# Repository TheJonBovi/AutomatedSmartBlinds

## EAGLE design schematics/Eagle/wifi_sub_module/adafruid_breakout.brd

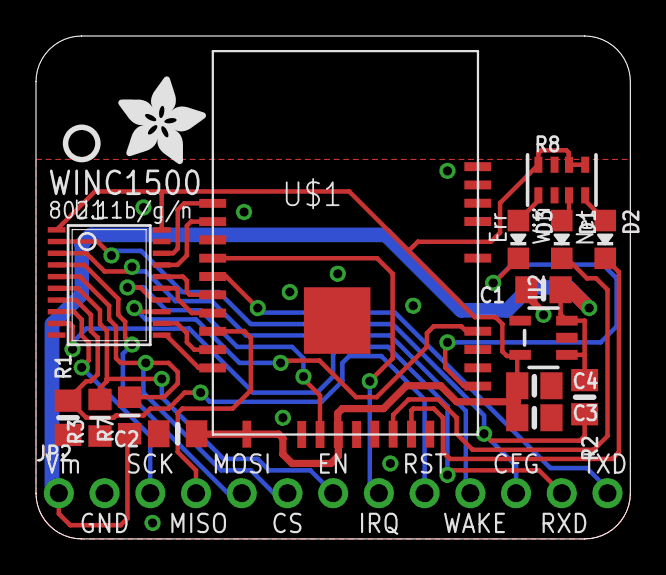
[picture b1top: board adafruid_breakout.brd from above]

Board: 2 copper layers, 33.0 x 27.9 mm, 19 parts (1 on the bottom side), 28 nets.

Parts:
C1, C3: 10uF; 0805-NO
C2: 10uF; 0805_10MGAP
C4: 0.1uF; 0805-NO
D1: green; CHIPLED_0805_NOOUTLINE
D2: Yellow; CHIPLED_0805_NOOUTLINE
D3: Red; CHIPLED_0805_NOOUTLINE
JP2: 1X13_ROUND_70
R1, R2: 100K; 0805-NO
R3, R7: 100K; _0805MP
R8: 1K; RESPACK_4X0603
U1: 74LVC245; TSSOP20
U2: AP2112-3.3; SOT23-5
U$1: ATWINC1500_MR210PB; ATWINC1500_MR210PA
U$4: ADAFRUIT_5MM
U$5: PCBFEAT-REV-040
U$6: ADAFRUIT_TEXT_20MM

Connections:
!IRQ: JP2.8, U$1.J13
+3V3: C2.1, C3.1, C4.1, R8.5, R8.6, R8.8, U1.1, U1.20, U2.5, U$1.J20, U$1.J23
+5V: C1.1, JP2.1, R2.1, R7.1, U2.1, U2.3
CFG_3V: U1.18, U$1.J10
CFG_5V: JP2.11, R2.2, U1.2
CS_3V: U1.15, U$1.J16
CS_5V: JP2.6, R7.2, U1.5
EN_3V: U1.14, U$1.J22
EN_5V: JP2.7, R3.2, U1.6
GND: C1.2, C2.2, C3.2, C4.2, JP2.2, R1.1, R3.1, U1.10, U1.19, U2.2, U$1.J9, U$1.J12, U$1.J28, U$1.MTGND
GPIO15: D1.C, U$1.J26
GPIO16: D2.C, U$1.J27
GPIO18: D3.C, U$1.J1
MISO: JP2.4, U$1.J17
MOSI_3V: U1.16, U$1.J15
MOSI_5V: JP2.5, U1.4
unnamed: D3.A, R8.1
unnamed: D2.A, R8.4
unnamed: D1.A, R8.3
RST_3V: U1.13, U$1.J4
RST_5V: JP2.9, R1.2, U1.7
RXD_3V: U1.11, U$1.J19
RXD_5V: JP2.12, U1.9
SCK_3V: U1.12, U$1.J18
SCK_5V: JP2.3, U1.8
TXD: JP2.13, U$1.J14
WAKE_3V: U1.17, U$1.J11
WAKE_5V: JP2.10, U1.3

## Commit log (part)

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2019-10-24 added documentation folder
    added folder and PIC32MZ datasheet as an example.
2019-10-25 Added datasheets
    Added datasheets for Drew components.
    Started MPLAB project for EFG version of software.
2019-10-31 Create 50002616A(WINC1500 Xplained Pro).pdf
    Added datashhet, this is a description of module and links to all other Datasheets
2019-10-31 Create Atmel-42420-WINC1500-Software-Design-Guide_UserGuide(WINC1500).pdf
    Software specs and design considerations
2019-10-31 Create PIC32MZ to WINC1500(WINC1500 to PIC).pdf
    examples of connecting to PIC MZ
2019-10-31 Create Wi-Fi_Network_Controller_Software_Prog_Guide(WINC1500).pdf
    Software programming guide
2019-10-31 Create junior_project.xlsx
    Gantt Chart started week 5 for schedule will update every meeting
2019-11-04 created main, config and ISR files
    Created the basis for the rest of the project, including a main routine to perform the RTS loop, as well as a config and ISR file to handle their respective duties.
    Also configured PBCLK3 and T2 and T3 according to CST337 lab as a proof-of-concept test. All configurations appear to be working so far in the simulator.
    Also added a specific datasheet for the ADC unit to the documentation folder.
2019-11-07 Create AutomatedSmartBlinds.sln
    Start of Visual Studio project
2019-11-07 Update junior_project.xlsx
    Updated junior project plan
2019-11-08 Started new projects and test stubs
    Started new projects and test stubs
2019-11-11 Began creating schematics in Eagle
    Began process of creating Eagle cad diagrams for each sub-module, starting with the stepper motors.
2019-11-12 added .h file for mask definitions
    added file to search and aid for the best modular code.
2019-11-13 initial ADC configuration written
    First three analog convertors (ADC0-2) configured for IR sensor inputs.
    Physical testing required.
2019-11-14 Update junior_project.xlsx
    Updated after team meeting
2019-11-14 Update Makefile-default.mk
    vesrion difference will update to compiler 2.3 to resolve
2019-11-14 Update Makefile-local-default.mk
    vesrion difference will update to compiler 2.3 to resolve
2019-11-15 ADC running (AN0 on ADC0)
    Confirmed running AN0 through ADC0. However, values range from 2048-4096, so some adjustment must be made.
    This does not currently scan the three analog inputs, just AN0
2019-11-15 minor ADC_config adjustments
    took out some unneccessary code.
2019-11-17 Update junior_project.xlsx
    added Drew sections for the Gantt Chart, as well as initial filling in of timeframes
2019-11-18 added the rest of the schematics
    created schematics for the remaining sub-modules. Also fixed up some pin assignments for other schematics.
    Added voltage divider to 5V analog sensors for 3.3V operation with PIC
2019-11-18 Update PIC32-HMZ144_Web(PIC32_Board_Info).pdf
    updated datasheet. Original was clipped off for some reason
2019-11-18 updated schematics with pinouts
    Added pintout information for motors.
2019-11-19 updated state machine diagram
    continued work on main state diagram
2019-11-20 updated schematics with pinouts
    contined adding pinout information.
    Still need: Buzzer, Wifi
2019-11-21 schematic fully pinned out
    added psuedocode to main to test output LED's.
    finished pinouts after input from team's sub-module requests.
2019-11-21 Stepper Motor Diagram
    Adding a stepper motor state diagram picture along with the visio file.
2019-11-21 added comment
    derp
2019-11-22 Stepper Motor .c File
    Adding the start of the stepper motor .c file. Will be updating this a lot more once the presentation is over.
2019-11-27 set up TMR2 interrupt loop for ADC polling
    Configured TMR2 to operate in 32 bit mode to time out every 0.5 seconds to form the sensor polling loop.
    Not fully tested on board yet.
2019-11-28 Pickit 3 Datasheet
    Here is the PICkit 3 user's guide/data sheet for programming the board.
2019-12-02 updated TMR2 operation for RTS loop
    Interrupt is triggereing but LED not toggling
2019-12-02 Update ISR.c
    added comment section to declare ISR priorites and shadowsets to avoid conflicts
2019-12-02 RK3 LED Flasher
    Added a new LED on RK3 that will flash every .5 seconds so we know the board is working.
2019-12-02 Stepper Motor Defines and Timer
    Set up the defines for each of the registers, and set up the timer function. Still need to set up the 8 cases for each signal step, and some extra parts.
2019-12-03 adjusted a schematic and added a datasheet
    scheamtic updated with values for buzzer.
    also uploading a worksheet that chad and I did for the motors and buzzer
2019-12-03 fixing project gitignore issues hold on
2019-12-03 testing gitignore issues
2019-12-03 final test
2019-12-05 Buzzer Implemented
    The buzzer is implemented in the ISR and the T4 config is done in the system_config
2019-12-12 updated drew side of schedule
2019-12-12 Moved schedule
    moved schedule and renamed for clarity
2019-12-12 added turn ins for semester
    seperated our documentation for turn-in this semester for plan, schedule and control. Also turned in to Phong
2019-12-17 started seperate project to config SPI for Camera
    Created SPI4 config file for use with the camera.
    Untested.
2020-01-07 Update Motor
    Changed the UDMOTOR settings for S7 from 13 to 12.
2020-01-07 added arduino stuff
2020-01-07 Buzzer test function complete
    Completed the buzzer function test to make sure that it produces sound. However, the dB seems to be a bit lower than what we were hoping. Might have to go with our alternative.
2020-01-08 minor changes
    forgot save before last commit
2020-01-11 added additional invoice
2020-01-11 Switch Statement and Gantt Chart
    Started making the switch statement for the stepper motor, started making the counter for the motor revolution, and finally made adjustments to the Gantt Chart.
2020-01-17 Temp, Gas, and DIP
    Worked on the system_configs for the temperature, gas, and DIP. Also made a blueprint for the temperature and gas sensors in the ISR. Lastly, made #defines for them as well in the defines file.
2020-01-17 added WINC1500 library ported from Atmel SAMD21
2020-01-22 Temperature and gas functions initial
    Here are the initial changes for the temperature and gas function. Still need to flesh out the rest of the functions to work properly.
2020-01-25 futher updating to PIC32
    Got most initialization done, still need to modify some defines. Also need to modify SPI routine to SPI4, instead of SPI2.
2020-01-29 Minor changes.
    Minor changes for the motor. Will be working on it more on the desktop.
2020-01-29 makefile conflict
2020-01-30 added some documentation for MLA WINC software
2020-01-31 success!
    PIC32 now successfully talks to the WINC1500 and can operate with the examples. Next step is to modify one of the demos to allow for sending data back and forth
2020-02-01 Motor full rotations complete
    Motors for both UD and OC will work both ways. There are also preset positions for each motor that can be used.
2020-02-01 upload new docs
    upload new docs
2020-02-01 Motor and Proxy Update
    Got the motors and the proxy to work together. Will fine tune it later.
2020-02-02 potential finish for migrating project
    migrated Smartblinds to WINCPORTED
2020-02-03 fixed up the speed of the motor
    full functional to continue development with all currently supported modules
2020-02-04 Monday work
    Got the motors redone with the proxy sensor. Also worked on timers 2, 3, 4, and 5.
2020-02-11 Temp and Gas Sensor
    Temp and Gas sensors starting to work. Still need to fine test them for their exact values.
2020-02-13 added SPI1.c for Camera commmunication function
    added initialize and read write single byte routines. Test read of the CHIP ID register (should output 0x40) is implemented but not tested as Camera is not attached to PIC yet.
2020-02-19 got SPI1 working
    Successfull communication with the OV2640. Need to write the following modules:
    set JPEG mode
    set size of JPEG
    caputure image
    etc?....
2020-02-21 I2C communication success
    Created I2C routines to communicate with camera sensor.
    Communication working, Configuration at 99% but the clear_fifo_flag function does not assert CS high again and complete its transmission.
    Need to figure out why
2020-02-23 set up Weather Client Example
    winc1500_weather_client is the primary state machine for the winc.
    It is currently set to connect to my (drew's) personal router. Settings for connections should be changed in the above file
2020-02-26 camera init working. I2C1 and SPI1 working as expected
2020-02-27 Created functions for capturing an image
    I think i am succesfully capturing images from the camera, but am unable to view them without sending to website.
    I know that the read_fifo_burst is successfully SPI'ing, as I can do other operations after like clear the fifo flag.
    I may need a bit of a delay in reading bytes out of the FIFO buffer, will determine once I can view the images
2020-02-27 commented out tests so project can be used by others
2020-02-28 added buzzer initializer
    Testing for acutual blinds. Camera disabled as it is not hooked up yet
2020-03-03 WIFI CHANGES
2020-03-03 code currently updates log with function 1
2020-03-04 Motor broken
    The motors are broken and is needing to be further debugged.
2020-03-04 ported weather example start
    moved weather example to new file to adjust state machine to handle our three instructions
2020-03-04 Motors fixed
    The up down motor has been fixed by increasing the MOTOR_PR_SETTING (which is slowing down the motor) to allow the steps to not get stopped via the torque.
2020-03-05 Temperature Update
    Changed the temperature high and low settings for it to trigger the blinds to open or close.
2020-03-05 testing with sending and recieving to WSDL
2020-03-05 receive temperature and receive motor
    Set up the functions for both the temperature high setting and the 2 stepper motor settings that will allow them to be changed via the web server.
2020-03-05 major porject cleanup
2020-03-06 fixed a derp thing, for real this time
2020-03-06 WiFi test stub
2020-03-06 gas, temp and proxy 99% tested.
    Still need to test with actual motors and more regression testing.
2020-03-06 further organisation
    debouncing all proximity sensor sections
2020-03-06 final call control organized.
    sending and recieving to website working 100%
2020-03-07 working on uploading images
2020-03-08 modified the proxy settings
    reduced the delay on the ADC reads from 0.5 seconds to 1.5ms for more consistent reading and for averaging purposes.
    Modifyed behavior of Proxy alarm settings.
2020-04-29 added UART2 code back in
    Ordered and wired up a FTDI board to convert the UART2 output from code to a USB interface to read debugging output.
2020-05-01 updated schematics and uart routine
    pinout errors so had to correct.
    updated pintouts to reflect current board
2020-05-05 Updated Blinds
    Updated the blinds by setting the newMotorTargetUD/OC to their proper default settings to eliminate the default setting of 0 when the blinds are not connected to the wifi.
2020-05-05 Images and page updates
    put your weight on it!
2020-05-06 lets do it
    try again
2020-05-06 new update
    new update
2020-05-06 updated contact info
    updated contact info
2020-05-06 contact update
    contact update
2020-05-10 updated beta site
    gas widget working
2020-05-14 added debug information
    continuing to test sdingin images
2020-05-15 more work to get image transfer to work
    images confirmed to be taken successfully, but still not able to transfer via a GET request.
    To test camera, comment out call_control call in main, and comment the message_type to IMG_UPLOAD in defines.h
2020-05-30 A simple way to manage code
    A simple way to manage code
2020-06-02 added document for semester 3 turn in
    added chads converted word doc

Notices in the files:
parts and their libraries:
microbuilder: This work is placed in the public domain, and may be freely used for commercial and non-commercial work with the following conditions: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
